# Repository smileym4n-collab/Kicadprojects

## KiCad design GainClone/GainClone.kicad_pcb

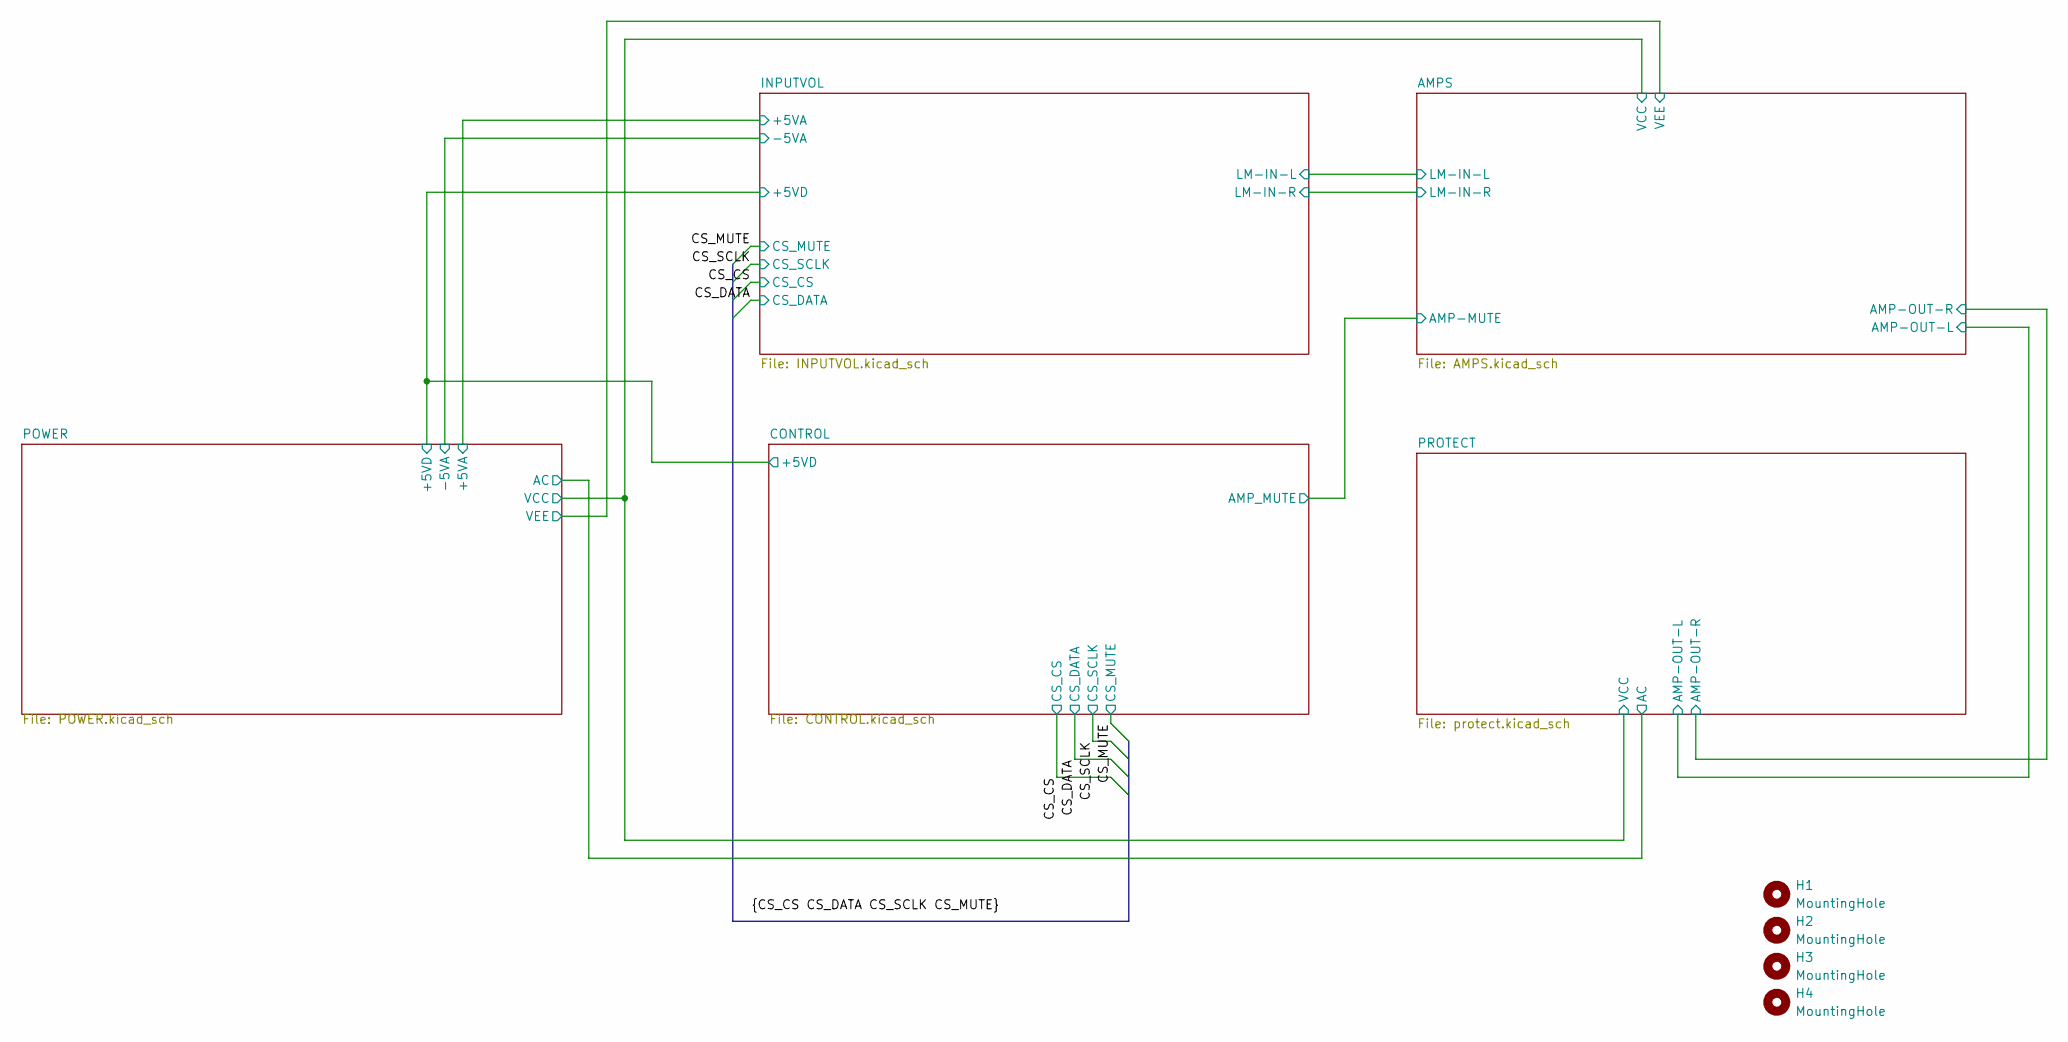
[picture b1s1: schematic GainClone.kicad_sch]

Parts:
H1, H2, H3, H4: MountingHole; MountingHole_3.2mm_M3

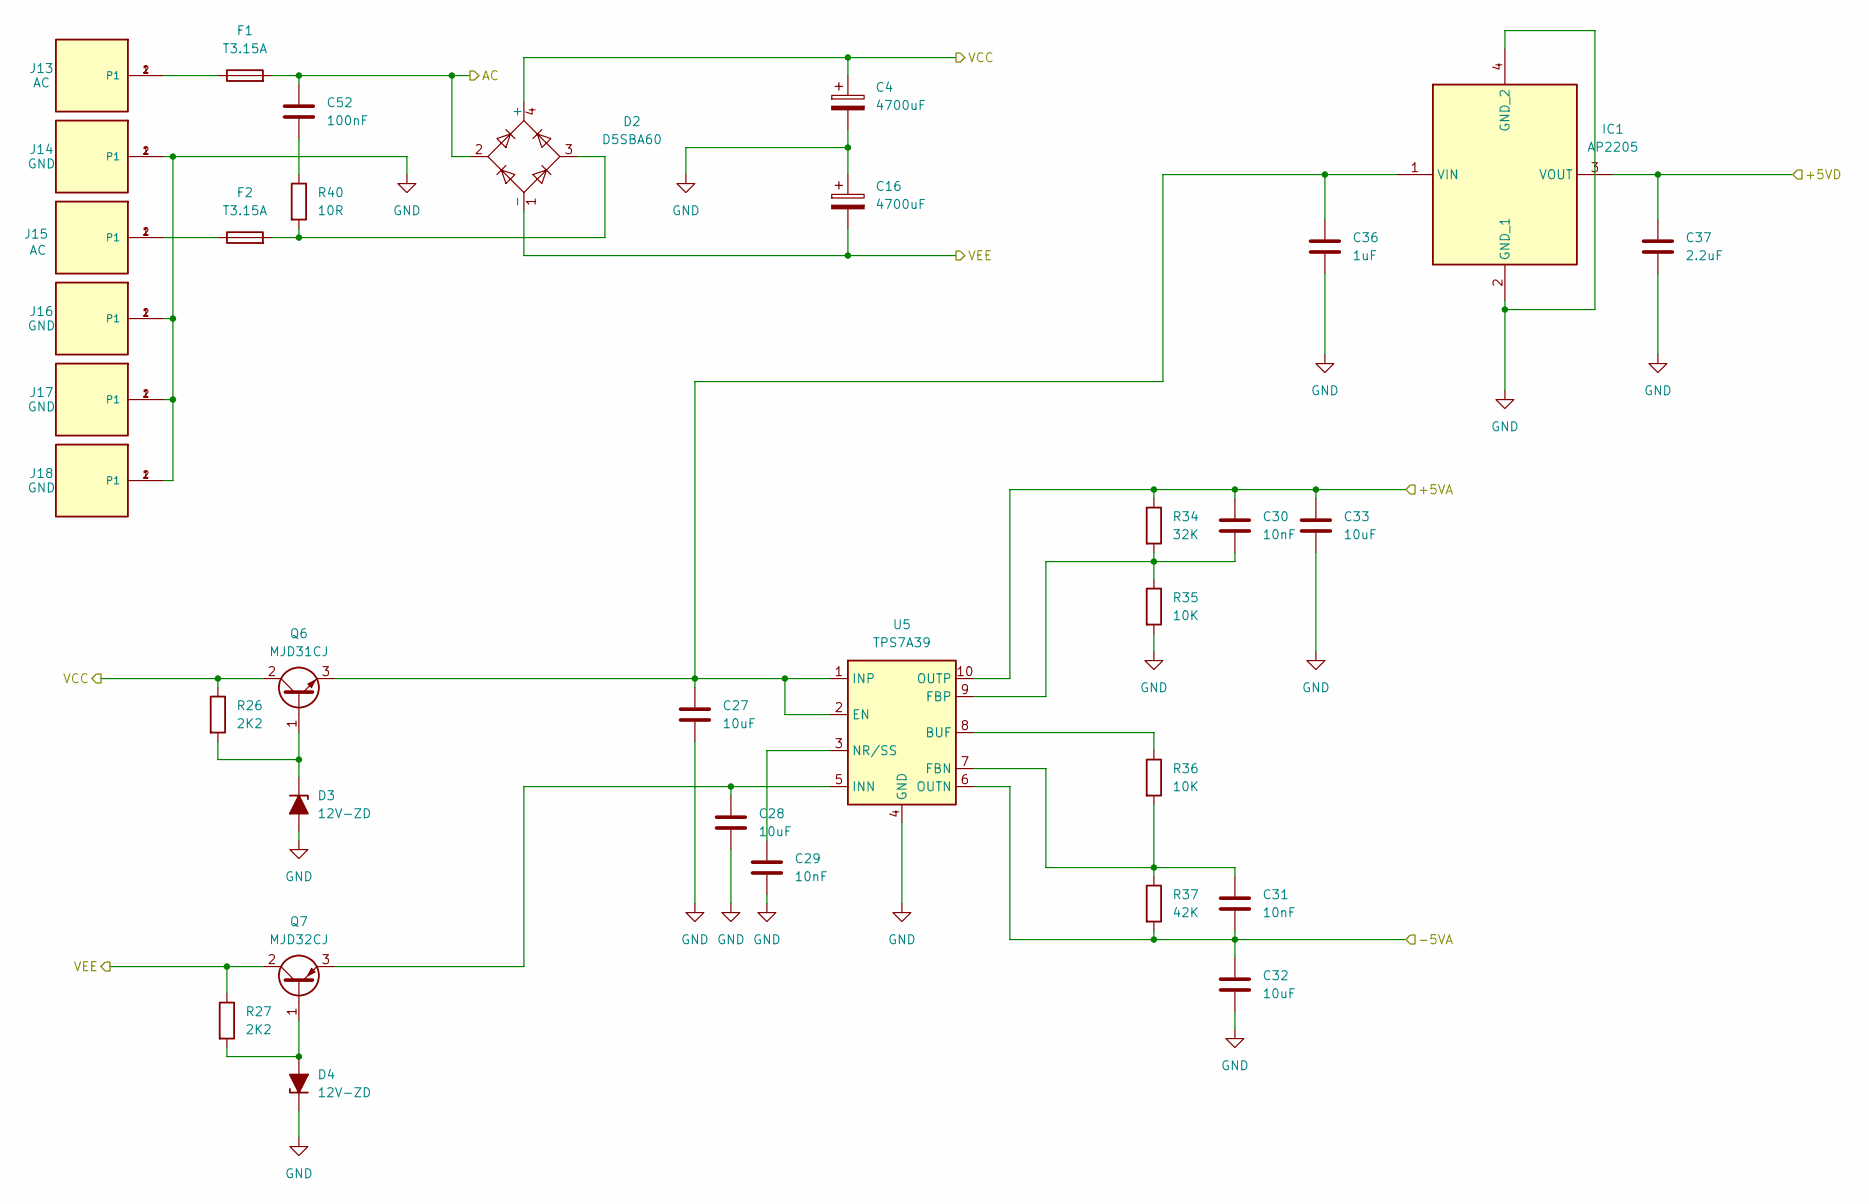
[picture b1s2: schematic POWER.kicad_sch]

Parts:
C4, C16: 4700uF; CP_Radial_D30.0mm_P10.00mm_SnapIn
C27, C28, C32, C33: 10uF; C_1206_3216Metric_Pad1.33x1.80mm_HandSolder
C29, C30, C31: 10nF; C_0805_2012Metric_Pad1.18x1.45mm_HandSolder
C36: 1uF; C_1206_3216Metric_Pad1.33x1.80mm_HandSolder
C37: 2.2uF; C_0805_2012Metric_Pad1.18x1.45mm_HandSolder
C52: 100nF; C_Rect_L18.0mm_W5.0mm_P15.00mm_FKS3_FKP3
D2: D5SBA60; Diode_Bridge_32.0x5.6x17.0mm_P10.0mm_P7.5mm
D3, D4: 12V-ZD; D_DO-201AD_P12.70mm_Horizontal
F1, F2: T3.15A; Fuse_Littelfuse_395Series
IC1: AP2205; SOT-89-3; Mouser Part Number 621-AP2205-50YR-13
J13, J15: AC; TE_62409-1; PART_DESCRIPTION CONN QC TAB 0.250 SOLDER
J14, J16, J17, J18: GND; TE_62409-1; PART_DESCRIPTION CONN QC TAB 0.250 SOLDER
Q6: MJD31CJ; TO-252-3_TabPin2
Q7: MJD32CJ; TO-252-3_TabPin2
R26, R27: 2K2; R_Axial_DIN0207_L6.3mm_D2.5mm_P10.16mm_Horizontal
R34: 32K; R_0805_2012Metric_Pad1.20x1.40mm_HandSolder
R35, R36: 10K; R_0805_2012Metric_Pad1.20x1.40mm_HandSolder
R37: 42K; R_0805_2012Metric_Pad1.20x1.40mm_HandSolder
R40: 10R; R_Axial_DIN0617_L17.0mm_D6.0mm_P20.32mm_Horizontal
U5: TPS7A39; Texas_S-PVSON-N10_ThermalVias

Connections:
/AMPS/VCC: C4.1, D2.4 (+), Q6.2 (C), R26.1; also elsewhere on the board
/AMPS/VEE: C16.2, D2.1 (-), Q7.2 (C), R27.1; also elsewhere on the board
/CONTROL/+5VD: C37.1, IC1.3 (VOUT); also elsewhere on the board
/INPUTVOL/+5VA: C30.1, C33.1, R34.1, U5.10 (OUTP); also elsewhere on the board
/INPUTVOL/-5VA: C31.2, C32.1, R37.2, U5.6 (OUTN); also elsewhere on the board
/POWER/AC: C52.1, D2.2, F1.2; also elsewhere on the board
GND: C4.2, C16.1, C27.2, C28.2, C29.2, C32.2, C33.2, C36.2, C37.2, D3.2 (A), D4.1 (K), IC1.2 (GND_1), IC1.4 (GND_2), J14.1, J14.2 (P1), J16.1, J16.2 (P1), J17.1, J17.2 (P1), J18.1, J18.2 (P1), R35.2, U5.4 (GND), U5.11 (GND); also elsewhere on the board
unnamed: C52.2, R40.1
unnamed: D2.3, F2.2, R40.2
unnamed: D3.1 (K), Q6.1 (B), R26.2
unnamed: D4.2 (A), Q7.1 (B), R27.2
unnamed: F1.1, J13.1, J13.2 (P1)
unnamed: F2.1, J15.1, J15.2 (P1)
unnamed: C27.1, C36.1, IC1.1 (VIN), Q6.3 (E), U5.1 (INP), U5.2 (EN)
unnamed: C28.1, Q7.3 (E), U5.5 (INN)
unnamed: R36.1, U5.8 (BUF)
unnamed: C31.1, R36.2, R37.1, U5.7 (FBN)
unnamed: C30.2, R34.2, R35.1, U5.9 (FBP)
unnamed: C29.1, U5.3 (NR/SS)

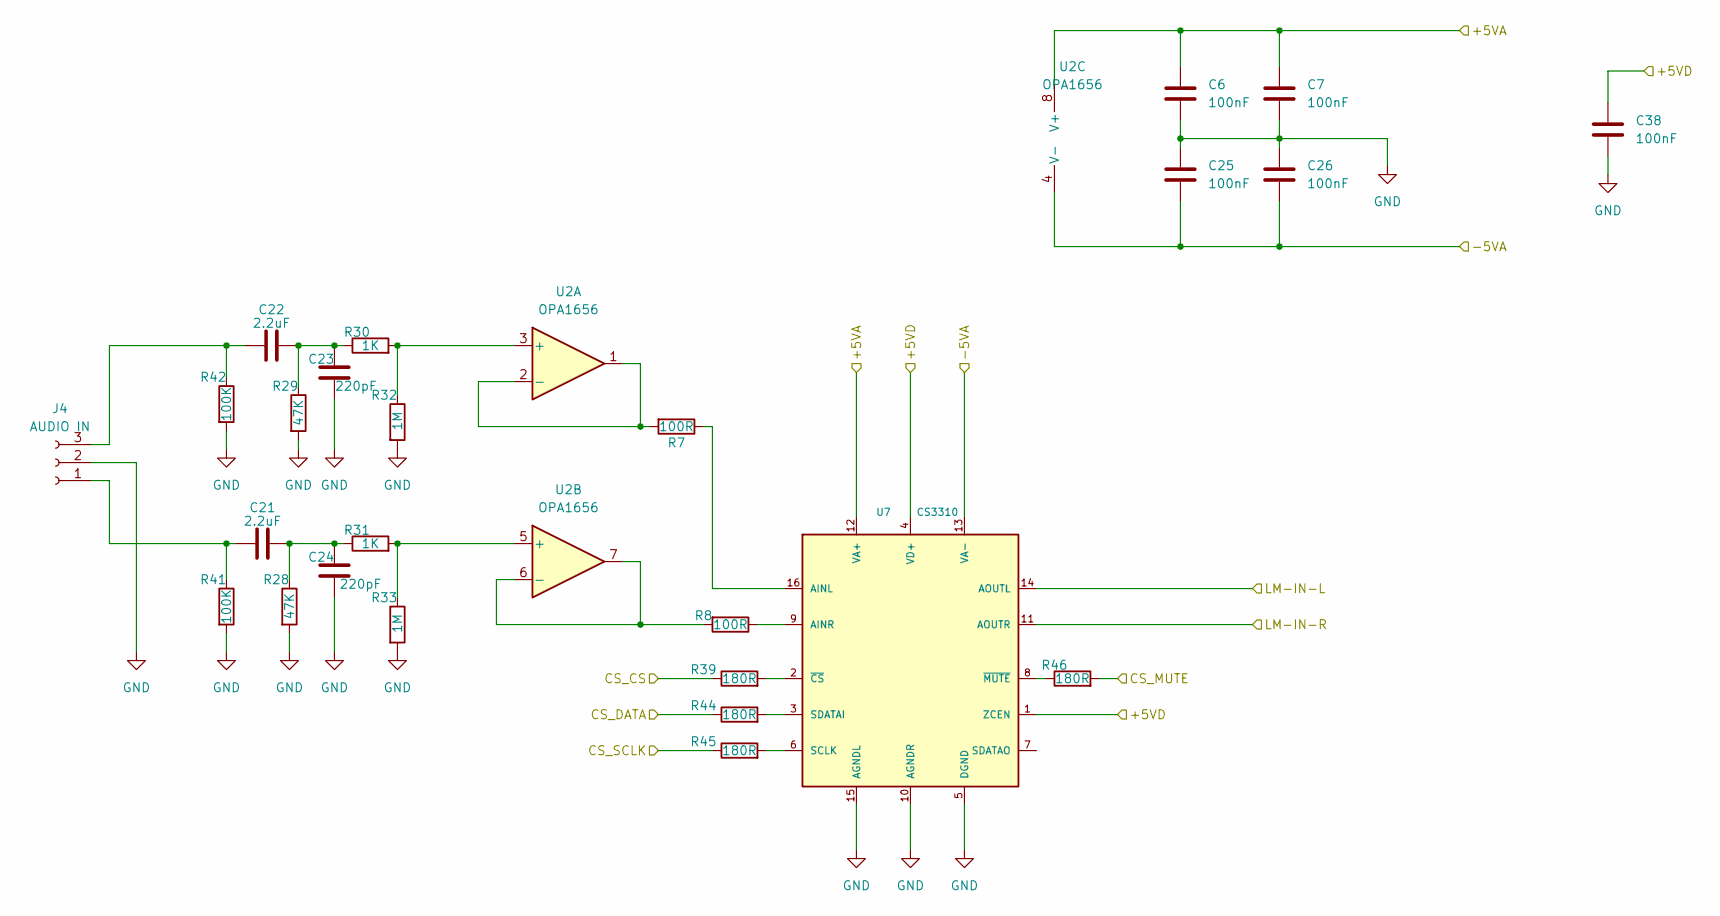
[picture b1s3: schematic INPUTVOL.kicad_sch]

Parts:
C6, C7, C25, C26, C38: 100nF; C_1206_3216Metric_Pad1.33x1.80mm_HandSolder
C21, C22: 2.2uF; C_Rect_L7.2mm_W7.2mm_P5.00mm_FKS2_FKP2_MKS2_MKP2
C23, C24: 220pF; C_0805_2012Metric_Pad1.18x1.45mm_HandSolder
J4: AUDIO IN; JST_XH_B3B-XH-A_1x03_P2.50mm_Vertical
R7, R8: 100R; R_0805_2012Metric_Pad1.20x1.40mm_HandSolder
R28, R29: 47K; R_0805_2012Metric_Pad1.20x1.40mm_HandSolder
R30, R31: 1K; R_0805_2012Metric_Pad1.20x1.40mm_HandSolder
R32, R33: 1M; R_0805_2012Metric_Pad1.20x1.40mm_HandSolder
R39, R44, R45, R46: 180R; R_0805_2012Metric_Pad1.20x1.40mm_HandSolder
R41, R42: 100K; R_0805_2012Metric_Pad1.20x1.40mm_HandSolder
U2: OPA1656; SOIC-8_3.9x4.9mm_P1.27mm
U7: CS3310; SOIC-16W_7.5x10.3mm_P1.27mm

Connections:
/AMPS/LM-IN-L: U7.14 (AOUTL); also elsewhere on the board
/AMPS/LM-IN-R: U7.11 (AOUTR); also elsewhere on the board
/CONTROL/+5VD: C38.1, U7.1 (ZCEN), U7.4 (VD+); also elsewhere on the board
/CS_CS: R39.1; also elsewhere on the board
/CS_DATA: R44.1; also elsewhere on the board
/CS_MUTE: R46.2; also elsewhere on the board
/CS_SCLK: R45.1; also elsewhere on the board
/INPUTVOL/+5VA: C6.1, C7.1, U2.8 (V+), U7.12 (VA+); also elsewhere on the board
/INPUTVOL/-5VA: C25.2, C26.2, U2.4 (V-), U7.13 (VA-); also elsewhere on the board
GND: C6.2, C7.2, C23.2, C24.2, C25.1, C26.1, C38.2, J4.2, R28.2, R29.2, R32.2, R33.2, R41.2, R42.2, U7.5 (DGND), U7.10 (AGNDR), U7.15 (AGNDL); also elsewhere on the board
unnamed: C21.2, C24.1, R28.1, R31.1
unnamed: C22.2, C23.1, R29.1, R30.1
unnamed: C21.1, J4.1, R41.1
unnamed: C22.1, J4.3, R42.1
unnamed: R30.2, R32.1, U2.3 (+)
unnamed: R7.2, U2.1, U2.2 (-)
unnamed: R31.2, R33.1, U2.5 (+)
unnamed: R8.2, U2.6 (-), U2.7
unnamed: R7.1, U7.16 (AINL)
unnamed: R8.1, U7.9 (AINR)
unnamed: R45.2, U7.6 (SCLK)
unnamed: R44.2, U7.3 (SDATAI)
unnamed: R39.2, U7.2 (~CS)
unnamed: R46.1, U7.8 (~MUTE)

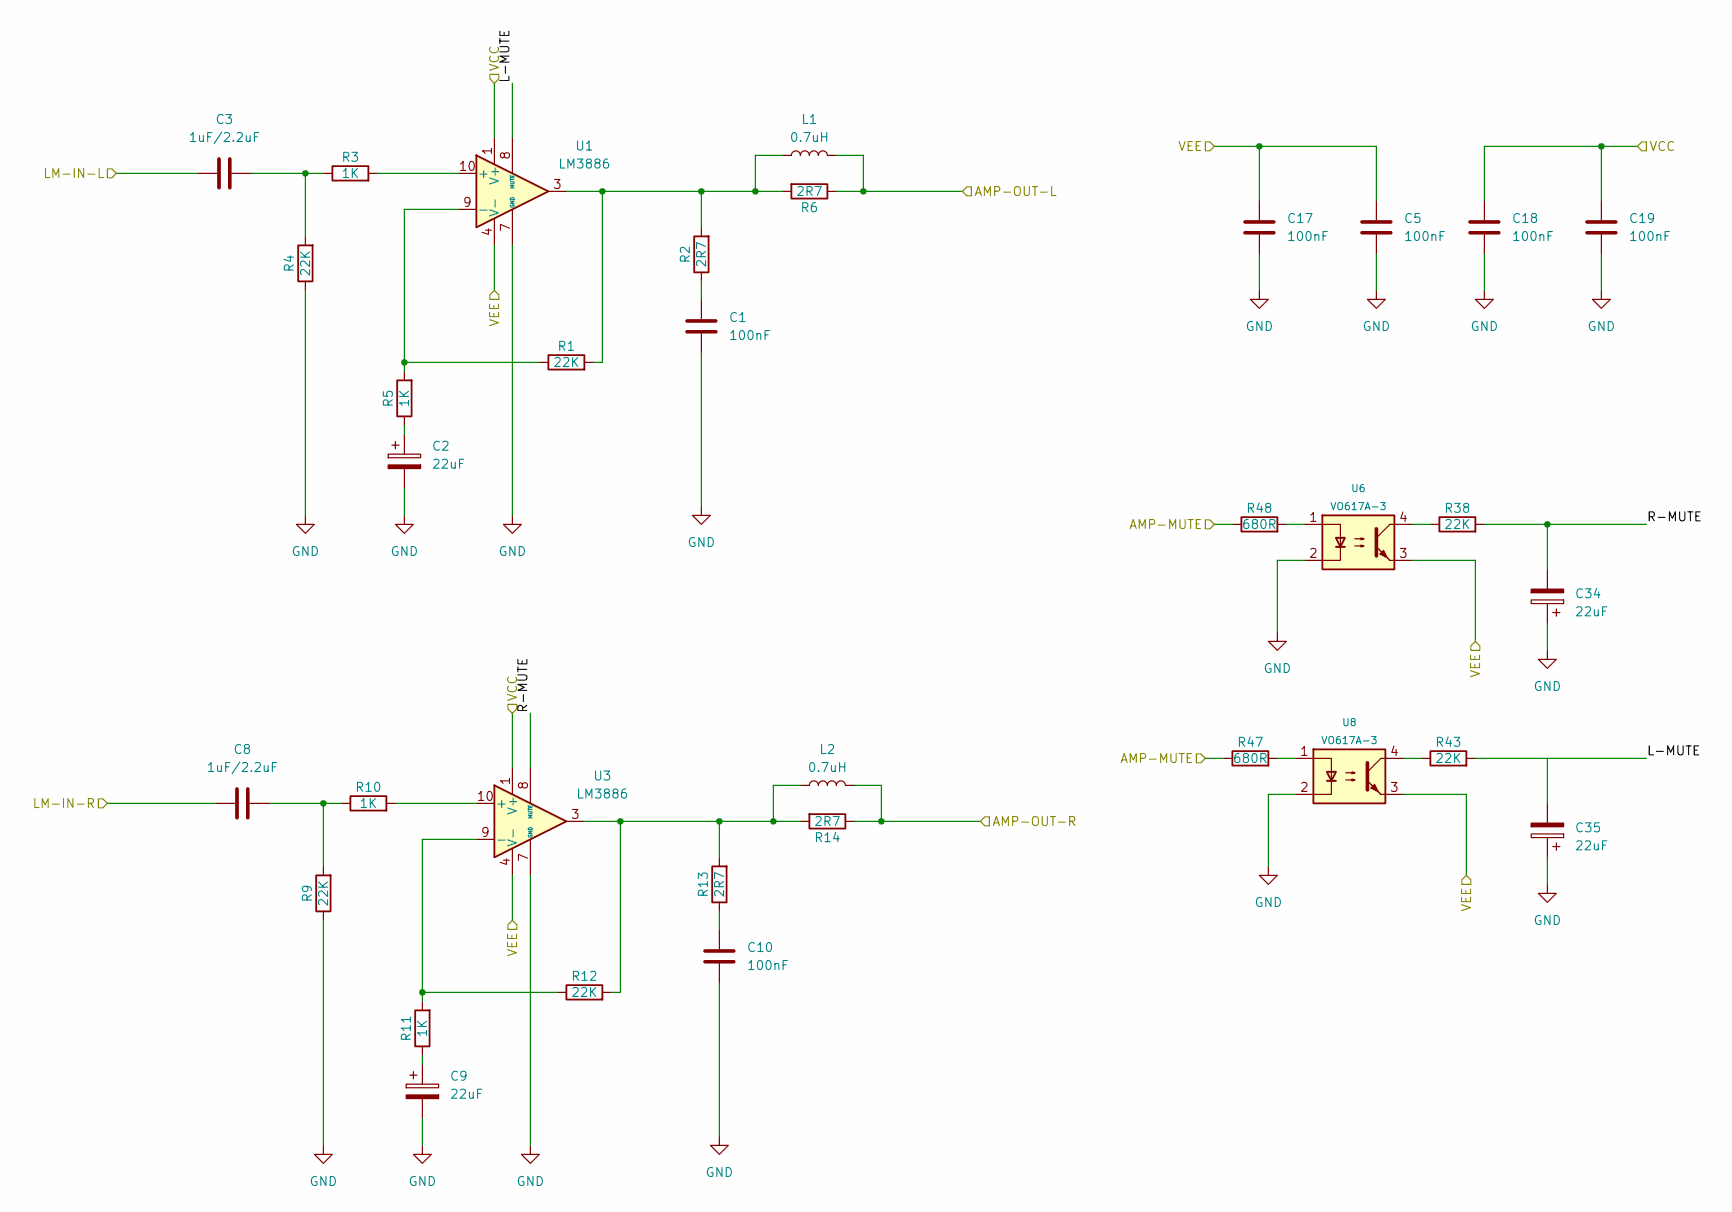
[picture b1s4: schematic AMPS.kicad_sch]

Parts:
C1, C10: 100nF; C_Rect_L7.2mm_W2.5mm_P5.00mm
C2, C9, C34, C35: 22uF; CP_Radial_D5.0mm_P2.50mm
C3, C8: 1uF/2.2uF; C_Rect_L7.2mm_W7.2mm_P5.00mm_FKS2_FKP2_MKS2_MKP2
C5, C17, C18, C19: 100nF; C_1206_3216Metric_Pad1.33x1.80mm_HandSolder
L1, L2: 0.7uH
R1, R4, R9, R12, R38, R43: 22K; R_0805_2012Metric_Pad1.20x1.40mm_HandSolder
R2, R6, R13, R14: 2R7; R_Axial_DIN0309_L9.0mm_D3.2mm_P12.70mm_Horizontal
R3, R5, R10, R11: 1K; R_0805_2012Metric_Pad1.20x1.40mm_HandSolder
R47, R48: 680R; R_0805_2012Metric_Pad1.20x1.40mm_HandSolder
U1, U3: LM3886; TO-220-11_P3.4x5.08mm_StaggerOdd_Lead4.58mm_Vertical
U6, U8: VO617A-3; DIP-4_W7.62mm

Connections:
/AMPS/AMP-MUTE: R47.1, R48.1; also elsewhere on the board
/AMPS/L-MUTE: C35.2, R43.2, U1.8 (MUTE)
/AMPS/LM-IN-L: C3.1; also elsewhere on the board
/AMPS/LM-IN-R: C8.1; also elsewhere on the board
/AMPS/R-MUTE: C34.2, R38.2, U3.8 (MUTE)
/AMPS/VCC: C18.1, C19.1, U1.1 (V+), U1.5 (V+), U3.1 (V+), U3.5 (V+); also elsewhere on the board
/AMPS/VEE: C5.1, C17.1, U1.4 (V-), U3.4 (V-), U6.3, U8.3; also elsewhere on the board
/PROTECT/L-IN: L1.2, R6.1; also elsewhere on the board
/PROTECT/R-IN: L2.2, R14.1; also elsewhere on the board
GND: C1.2, C2.2, C5.2, C9.2, C10.2, C17.2, C18.2, C19.2, C34.1, C35.1, R4.1, R9.1, U1.7 (GND), U3.7 (GND), U6.2, U8.2; also elsewhere on the board
unnamed: C1.1, R2.1
unnamed: C2.1, R5.1
unnamed: C3.2, R3.1, R4.2
unnamed: C8.2, R9.2, R10.1
unnamed: C9.1, R11.1
unnamed: C10.1, R13.1
unnamed: L1.1, R1.2, R2.2, R6.2, U1.3
unnamed: L2.1, R12.2, R13.2, R14.2, U3.3
unnamed: R38.1, U6.4
unnamed: R43.1, U8.4
unnamed: R47.2, U8.1
unnamed: R48.2, U6.1
unnamed: R3.2, U1.10 (+)
unnamed: R1.1, R5.2, U1.9 (-)
unnamed: R10.2, U3.10 (+)
unnamed: R11.2, R12.1, U3.9 (-)

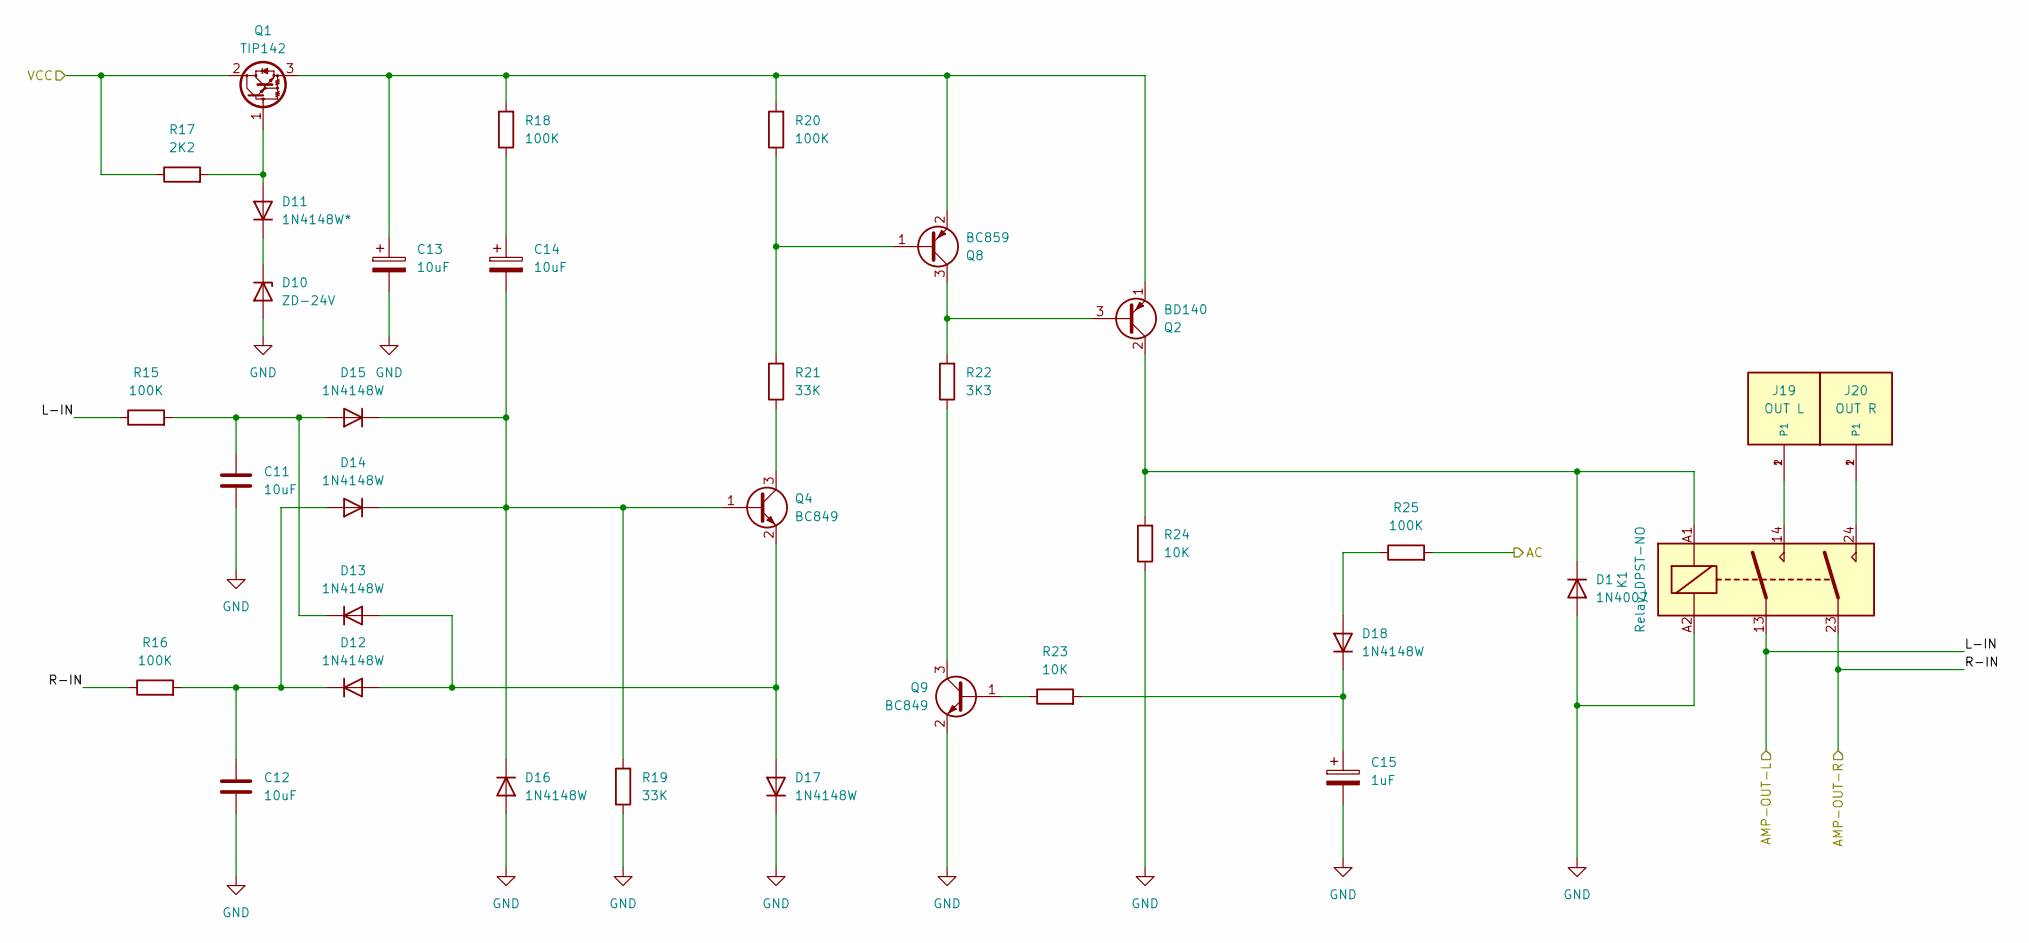
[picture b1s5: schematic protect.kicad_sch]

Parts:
C11, C12: 10uF; C_Radial_D6.3mm_H7.0mm_P2.50mm
C13, C14: 10uF; CP_Radial_D5.0mm_P2.00mm
C15: 1uF; CP_Radial_D5.0mm_P2.00mm
D1: 1N4007; D_DO-41_SOD81_P10.16mm_Horizontal
D10: ZD-24V; D_DO-41_SOD81_P10.16mm_Horizontal
D11: 1N4148W*; D_SOD-123
D12, D13, D14, D15, D16, D17, D18: 1N4148W; D_SOD-123
J19: OUT L; TE_62409-1; PART_DESCRIPTION CONN QC TAB 0.250 SOLDER
J20: OUT R; TE_62409-1; PART_DESCRIPTION CONN QC TAB 0.250 SOLDER
K1: Relay_DPST-NO; SPKPRTCRELAY
Q1: TIP142; TO-220-3_Vertical
Q2: BD140; TO-126-3_Vertical
Q4, Q9: BC849; SOT-23
Q8: BC859; SOT-23
R15, R16, R18, R20, R25: 100K; R_0805_2012Metric_Pad1.20x1.40mm_HandSolder
R17: 2K2; R_Axial_DIN0207_L6.3mm_D2.5mm_P10.16mm_Horizontal
R19, R21: 33K; R_0805_2012Metric_Pad1.20x1.40mm_HandSolder
R22: 3K3; R_0805_2012Metric_Pad1.20x1.40mm_HandSolder
R23, R24: 10K; R_0805_2012Metric_Pad1.20x1.40mm_HandSolder

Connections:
/AMPS/VCC: Q1.2 (C), R17.1; also elsewhere on the board
/POWER/AC: R25.2; also elsewhere on the board
/PROTECT/L-IN: K1.13, R15.1; also elsewhere on the board
/PROTECT/R-IN: K1.23, R16.1; also elsewhere on the board
GND: C11.1, C12.1, C13.2, C15.2, D1.2 (A), D10.2 (A), D16.2 (A), D17.1 (K), K1.A2, Q9.2 (E), R19.1, R24.1; also elsewhere on the board
unnamed: C14.1, R18.1
unnamed: D1.1 (K), K1.A1, Q2.2 (C), R24.2
unnamed: D10.1 (K), D11.1 (K)
unnamed: D11.2 (A), Q1.1 (B), R17.2
unnamed: D12.2 (A), D13.2 (A), D17.2 (A), Q4.2 (E)
unnamed: C12.2, D12.1 (K), D14.2 (A), R16.2
unnamed: C11.2, D13.1 (K), D15.2 (A), R15.2
unnamed: C14.2, D14.1 (K), D15.1 (K), D16.1 (K), Q4.1 (B), R19.2
unnamed: D18.2 (A), R25.1
unnamed: C15.1, D18.1 (K), R23.2
unnamed: J19.1, J19.2 (P1), K1.14
unnamed: J20.1, J20.2 (P1), K1.24
unnamed: C13.1, Q1.3 (E), Q2.1 (E), Q8.2 (E), R18.2, R20.2
unnamed: Q2.3 (B), Q8.3 (C), R22.2
unnamed: Q4.3 (C), R21.1
unnamed: Q8.1 (B), R20.1, R21.2
unnamed: Q9.1 (B), R23.1
unnamed: Q9.3 (C), R22.1

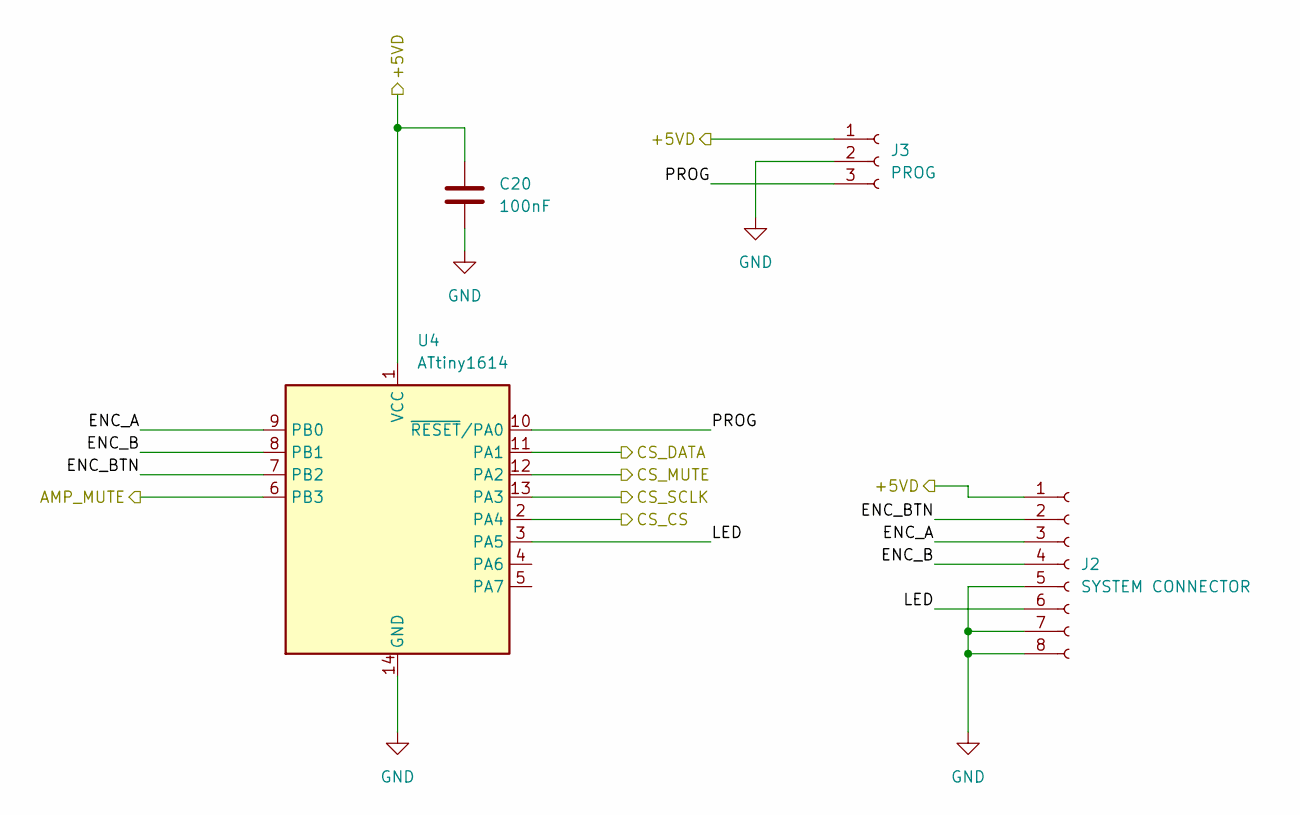
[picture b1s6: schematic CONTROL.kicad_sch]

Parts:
C20: 100nF; C_1206_3216Metric_Pad1.33x1.80mm_HandSolder
J2: SYSTEM CONNECTOR; JST_XH_B8B-XH-A_1x08_P2.50mm_Vertical
J3: PROG; PinHeader_1x03_P2.54mm_Vertical
U4: ATtiny1614; SOIC-14_3.9x8.7mm_P1.27mm

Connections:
/AMPS/AMP-MUTE: U4.6 (PB3); also elsewhere on the board
/CONTROL/+5VD: C20.1, J2.1, J3.1, U4.1 (VCC); also elsewhere on the board
/CONTROL/ENC_A: J2.3, U4.9 (PB0)
/CONTROL/ENC_B: J2.4, U4.8 (PB1)
/CONTROL/ENC_BTN: J2.2, U4.7 (PB2)
/CONTROL/LED: J2.6, U4.3 (PA5)
/CONTROL/PROG: J3.3, U4.10 (~RESET/PA0)
/CS_CS: U4.2 (PA4); also elsewhere on the board
/CS_DATA: U4.11 (PA1); also elsewhere on the board
/CS_MUTE: U4.12 (PA2); also elsewhere on the board
/CS_SCLK: U4.13 (PA3); also elsewhere on the board
GND: C20.2, J2.5, J2.7, J2.8, J3.2, U4.14 (GND); also elsewhere on the board

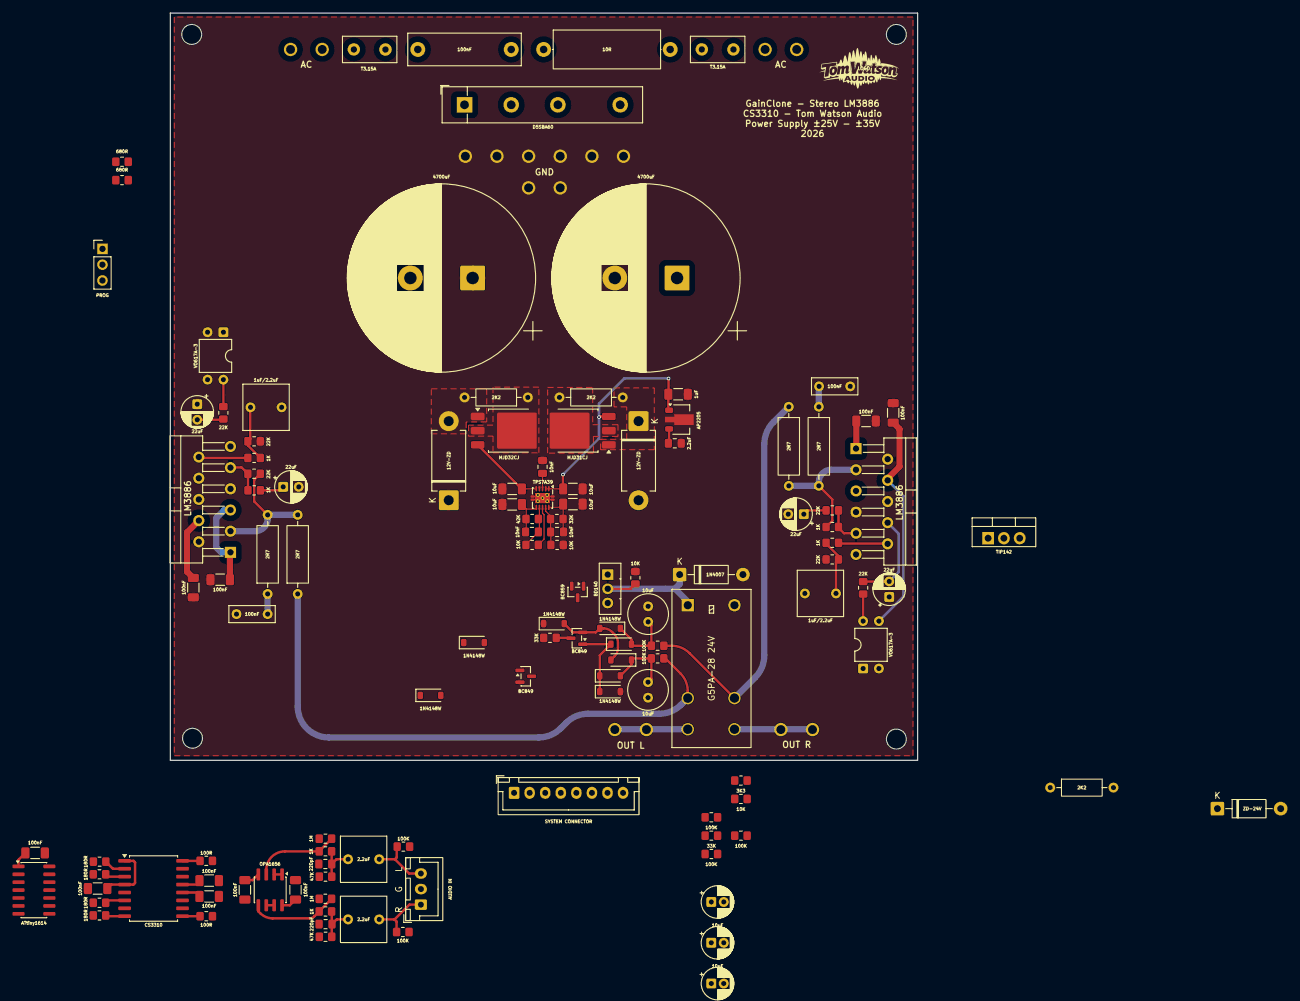
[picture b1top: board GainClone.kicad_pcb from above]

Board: 2 copper layers, 120.0 x 120.0 mm, 134 parts (0 on the bottom side), 83 nets.

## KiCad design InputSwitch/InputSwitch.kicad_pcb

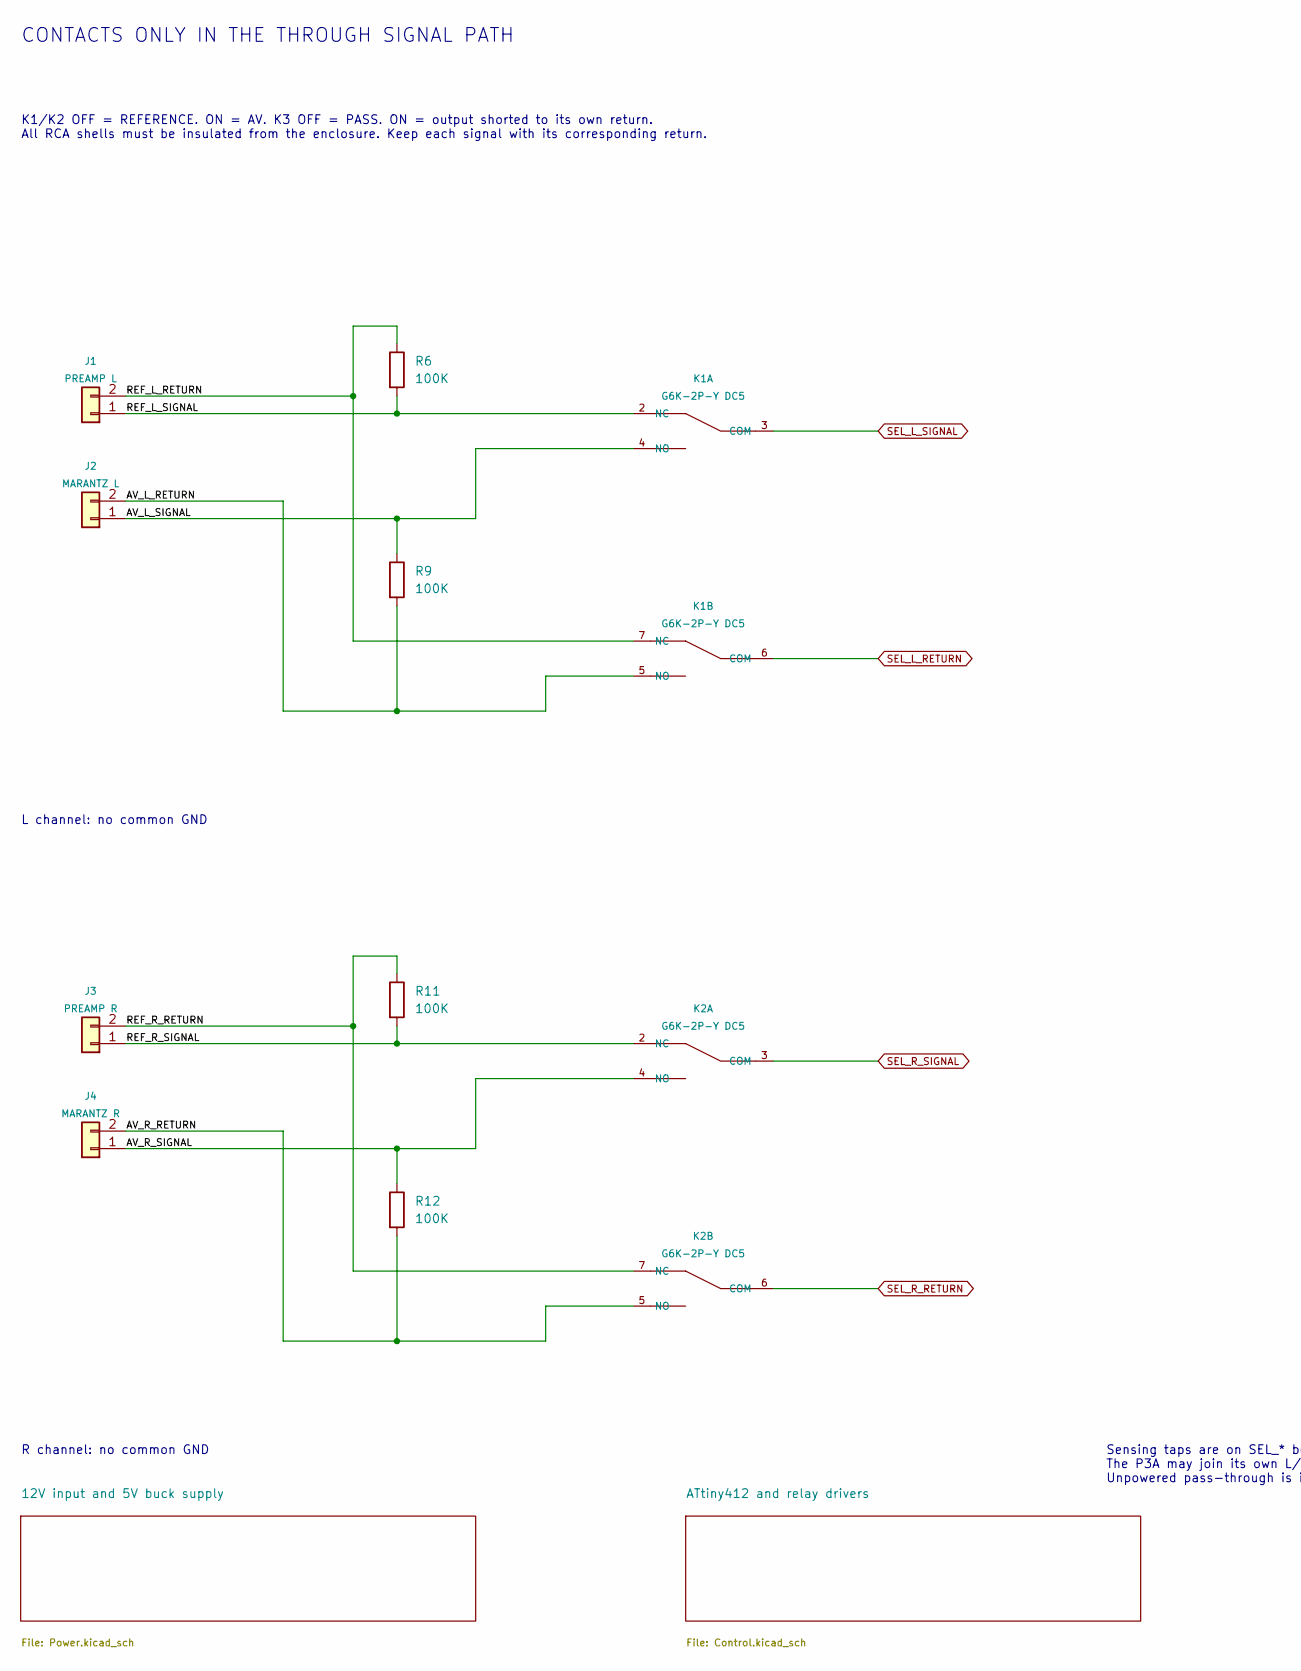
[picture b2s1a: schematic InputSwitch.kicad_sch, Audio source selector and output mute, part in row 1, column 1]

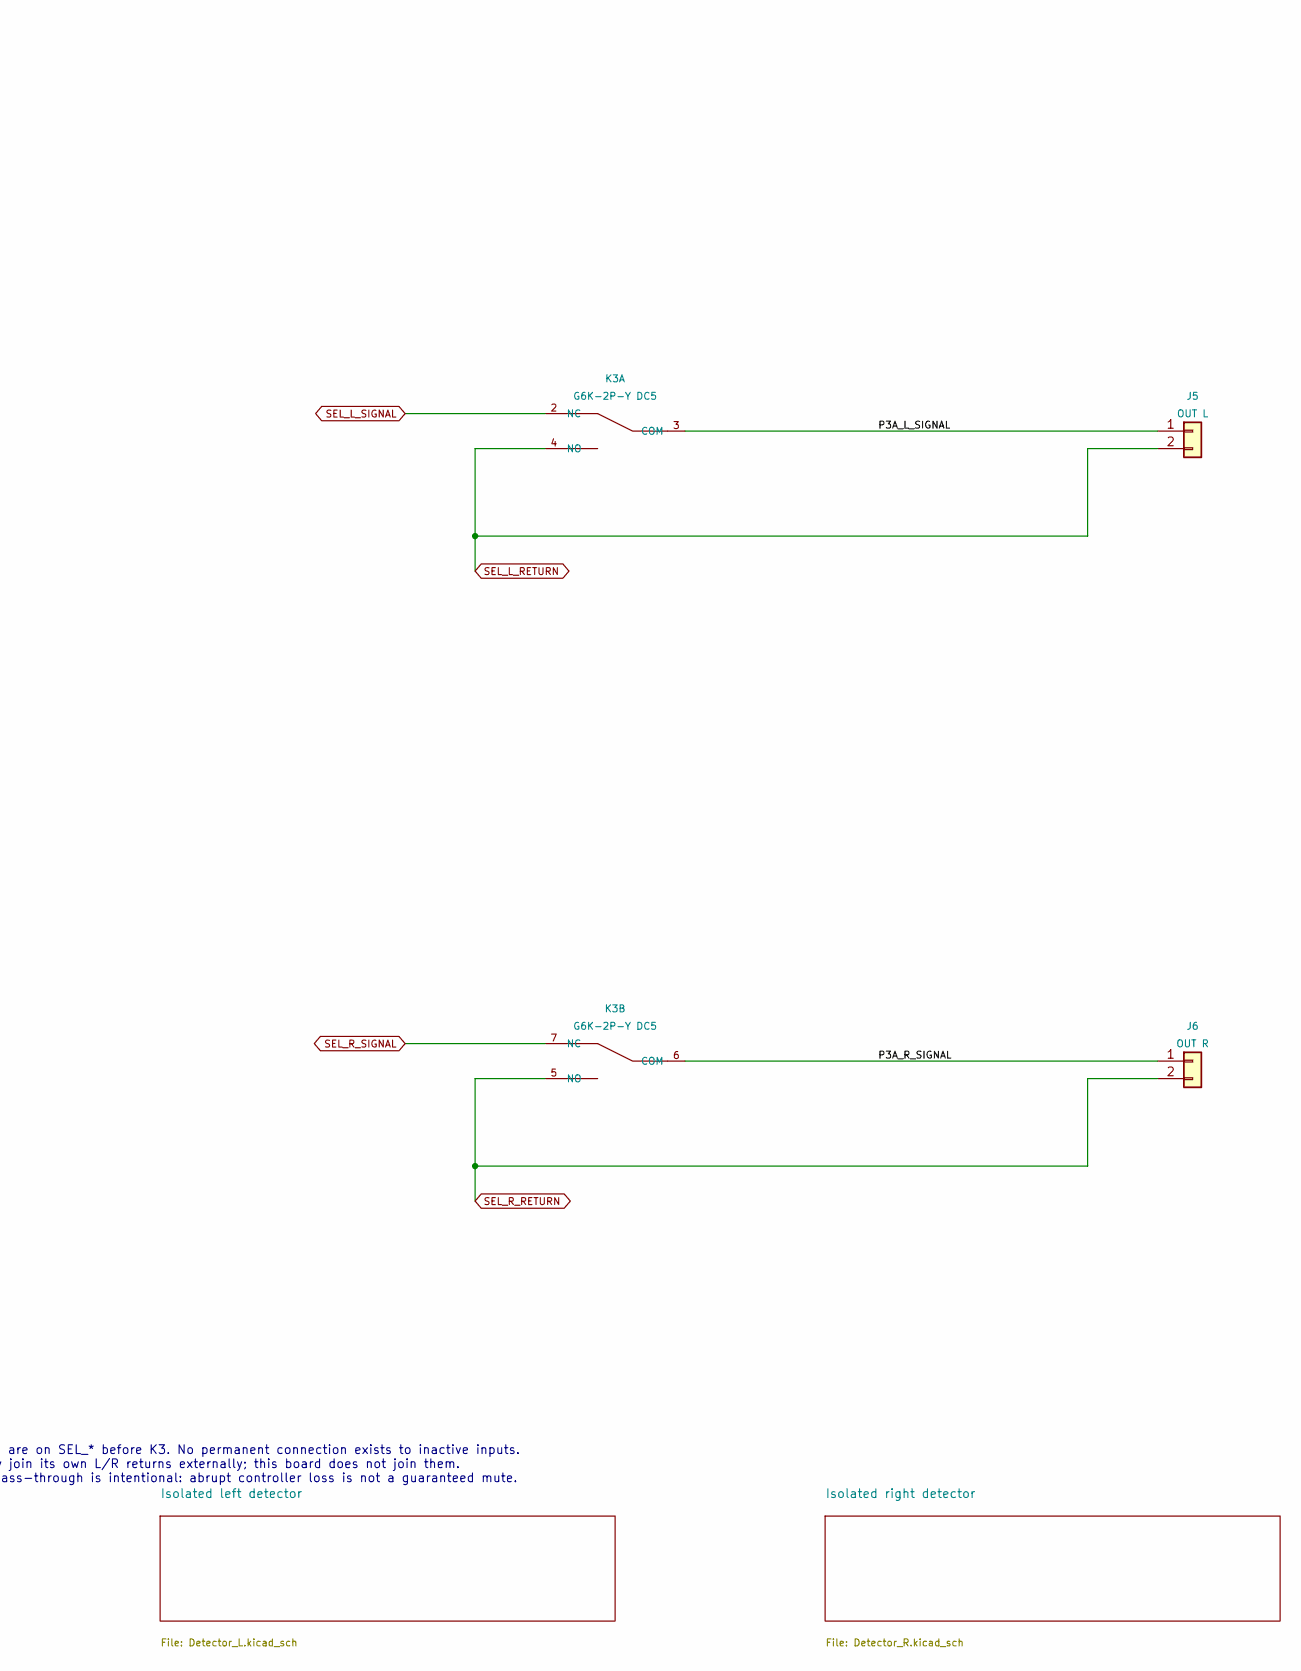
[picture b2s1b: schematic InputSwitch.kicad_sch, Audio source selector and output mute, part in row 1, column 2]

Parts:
J1: PREAMP L; JST_XH_B2B-XH-A_1x02_P2.50mm_Vertical
J2: MARANTZ L; JST_XH_B2B-XH-A_1x02_P2.50mm_Vertical
J3: PREAMP R; JST_XH_B2B-XH-A_1x02_P2.50mm_Vertical
J4: MARANTZ R; JST_XH_B2B-XH-A_1x02_P2.50mm_Vertical
J5: OUT L; JST_XH_B2B-XH-A_1x02_P2.50mm_Vertical
J6: OUT R; JST_XH_B2B-XH-A_1x02_P2.50mm_Vertical
K1, K2, K3: G6K-2P-Y DC5; Relay_DPDT_Omron_G6K-2P-Y_Datasheet
R6, R9, R11, R12: 100K; R_0805_2012Metric_Pad1.20x1.40mm_HandSolder

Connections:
/AV_L_RETURN: J2.2, K1.5 (NO), R9.2
/AV_L_SIGNAL: J2.1, K1.4 (NO), R9.1
/AV_R_RETURN: J4.2, K2.5 (NO), R12.2
/AV_R_SIGNAL: J4.1, K2.4 (NO), R12.1
/P3A_L_SIGNAL: J5.1, K3.3 (COM)
/P3A_R_SIGNAL: J6.1, K3.6 (COM)
/REF_L_RETURN: J1.2, K1.7 (NC), R6.1
/REF_L_SIGNAL: J1.1, K1.2 (NC), R6.2
/REF_R_RETURN: J3.2, K2.7 (NC), R11.1
/REF_R_SIGNAL: J3.1, K2.2 (NC), R11.2
SEL_L_RETURN: J5.2, K1.6 (COM), K3.4 (NO); also elsewhere on the board
SEL_L_SIGNAL: K1.3 (COM), K3.2 (NC); also elsewhere on the board
SEL_R_RETURN: J6.2, K2.6 (COM), K3.5 (NO); also elsewhere on the board
SEL_R_SIGNAL: K2.3 (COM), K3.7 (NC); also elsewhere on the board

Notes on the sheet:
CONTACTS ONLY IN THE THROUGH SIGNAL PATH
K1/K2 OFF = REFERENCE. ON = AV. K3 OFF = PASS. ON = output shorted to its own return. All RCA shells must be insulated from the enclosure. Keep each signal with its corresponding return.
R channel: no common GND
Sensing taps are on SEL_* before K3. No permanent connection exists to inactive inputs. The P3A may join its own L/R returns externally; this board does not join them. Unpowered pass-through is intentional: abrupt controller loss is not a guaranteed mute.
L channel: no common GND
